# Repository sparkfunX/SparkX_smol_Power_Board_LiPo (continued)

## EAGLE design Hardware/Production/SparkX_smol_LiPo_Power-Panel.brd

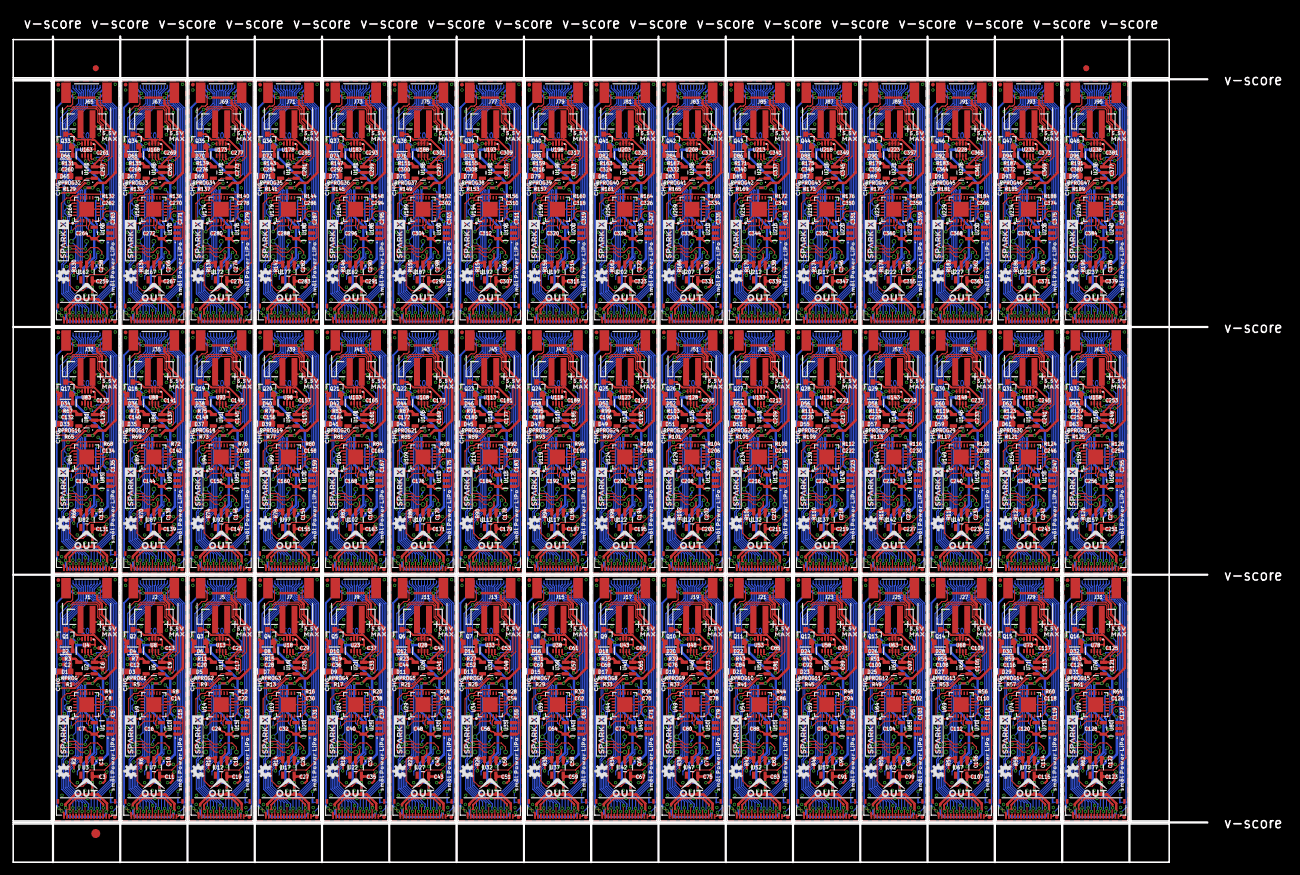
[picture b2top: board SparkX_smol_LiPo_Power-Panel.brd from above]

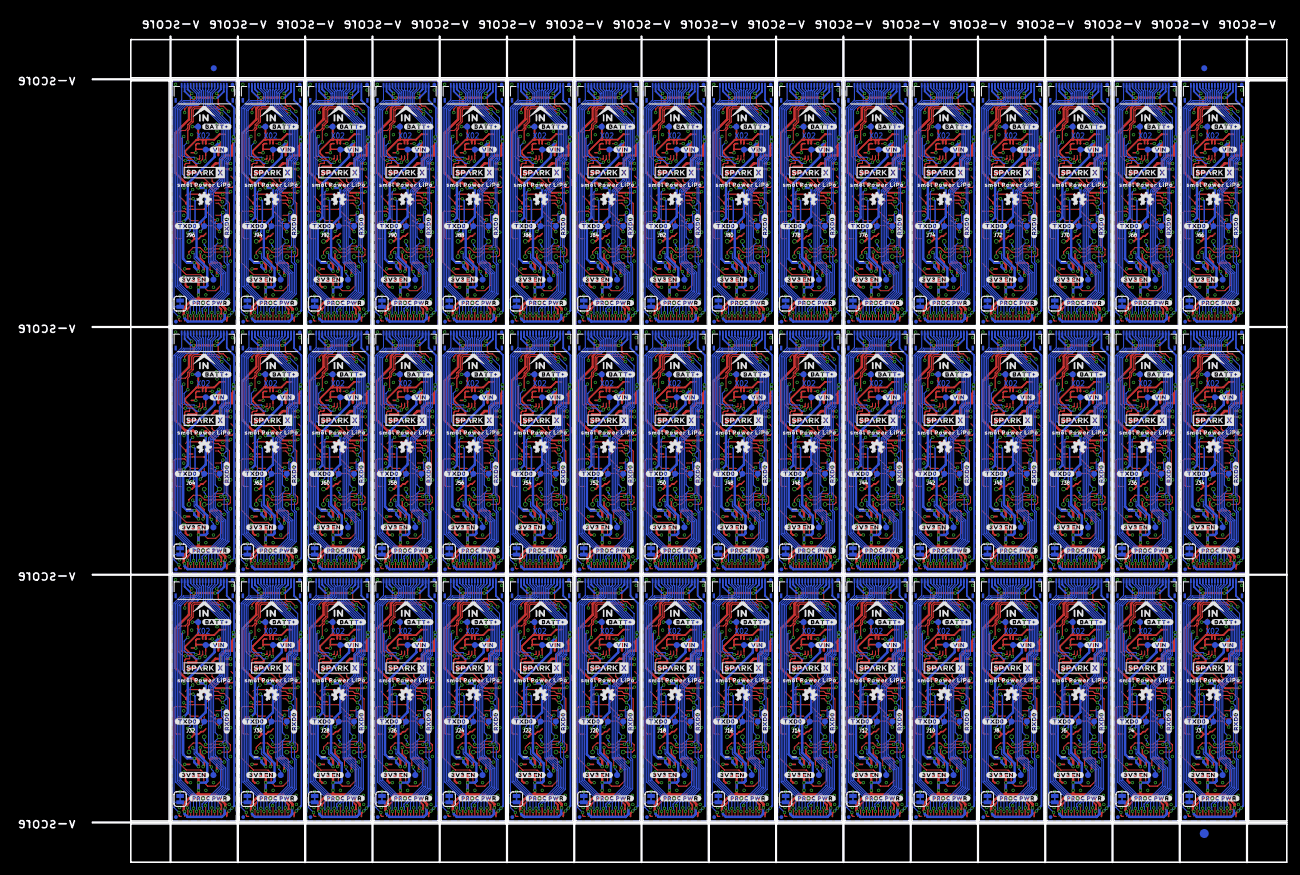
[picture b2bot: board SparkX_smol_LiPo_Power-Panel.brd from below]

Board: 2 copper layers, 198.4 x 137.2 mm, 2598 parts (1011 on the bottom side), 1200 nets.

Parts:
3V3_EN, 3V3_EN1, 3V3_EN2, 3V3_EN3, 3V3_EN4, 3V3_EN5, 3V3_EN6, 3V3_EN7, 3V3_EN8, 3V3_EN9, 3V3_EN10, 3V3_EN11, 3V3_EN12, 3V3_EN13, 3V3_EN14, 3V3_EN15, 3V3_EN16, 3V3_EN17, 3V3_EN18, 3V3_EN19, 3V3_EN20, 3V3_EN21, 3V3_EN22, 3V3_EN23, 3V3_EN24, 3V3_EN25, 3V3_EN26, 3V3_EN27, 3V3_EN28, 3V3_EN29, 3V3_EN30, 3V3_EN31, 3V3_EN32, 3V3_EN33, 3V3_EN34, 3V3_EN35, 3V3_EN36, 3V3_EN37, 3V3_EN38, 3V3_EN39, 3V3_EN40, 3V3_EN41, 3V3_EN42, 3V3_EN43, 3V3_EN44, 3V3_EN45, 3V3_EN46, 3V3_EN47: TEST-POINT3X4; PAD.03X.04
BATT+, BATT+1, BATT+2, BATT+3, BATT+4, BATT+5, BATT+6, BATT+7, BATT+8, BATT+9, BATT+10, BATT+11, BATT+12, BATT+13, BATT+14, BATT+15, BATT+16, BATT+17, BATT+18, BATT+19, BATT+20, BATT+21, BATT+22, BATT+23, BATT+24, BATT+25, BATT+26, BATT+27, BATT+28, BATT+29, BATT+30, BATT+31, BATT+32, BATT+33, BATT+34, BATT+35, BATT+36, BATT+37, BATT+38, BATT+39, BATT+40, BATT+41, BATT+42, BATT+43, BATT+44, BATT+45, BATT+46, BATT+47: TEST-POINT3X4; PAD.03X.04
C1, C2, C3, C5, C7, C10, C11, C12, C15, C16, C18, C19, C20, C23, C24, C26, C27, C28, C31, C32, C34, C35, C36, C39, C40, C42, C43, C44, C47, C48, C50, C51, C52, C55, C56, C58, C59, C60, C63, C64, C66, C67, C68, C71, C72, C74, C75, C76, C79, C80, C82, C83, C84, C87, C88, C90, C91, C92, C95, C96, C98, C99, C100, C103, C104, C106, C107, C108, C111, C112, C114, C115, C116, C119, C120, C122, C123, C124, C127, C128, C130, C131, C132, C135, C136, C138, C139, C140, C143, C144, C146, C147, C148, C151, C152, C154, C155, C156, C159, C160, C162, C163, C164, C167, C168, C170, C171, C172, C175, C176, C178, C179, C180, C183, C184, C186, C187, C188, C191, C192, C194, C195, C196, C199, C200, C202, C203, C204, C207, C208, C210, C211, C212, C215, C216, C218, C219, C220, C223, C224, C226, C227, C228, C231, C232, C234, C235, C236, C239, C240, C242, C243, C244, C247, C248, C250, C251, C252, C255, C256, C258, C259, C260, C263, C264, C266, C267, C268, C271, C272, C274, C275, C276, C279, C280, C282, C283, C284, C287, C288, C290, C291, C292, C295, C296, C298, C299, C300, C303, C304, C306, C307, C308, C311, C312, C314, C315, C316, C319, C320, C322, C323, C324, C327, C328, C330, C331, C332, C335, C336, C338, C339, C340, C343, C344, C346, C347, C348, C351, C352, C354, C355, C356, C359, C360, C362, C363, C364, C367, C368, C370, C371, C372, C375, C376, C378, C379, C380, C383, C384: 2.2uF; 0402-TIGHT
C4, C8, C13, C14, C21, C22, C29, C30, C37, C38, C45, C46, C53, C54, C61, C62, C69, C70, C77, C78, C85, C86, C93, C94, C101, C102, C109, C110, C117, C118, C125, C126, C133, C134, C141, C142, C149, C150, C157, C158, C165, C166, C173, C174, C181, C182, C189, C190, C197, C198, C205, C206, C213, C214, C221, C222, C229, C230, C237, C238, C245, C246, C253, C254, C261, C262, C269, C270, C277, C278, C285, C286, C293, C294, C301, C302, C309, C310, C317, C318, C325, C326, C333, C334, C341, C342, C349, C350, C357, C358, C365, C366, C373, C374, C381, C382: 0.1uF; 0402-TIGHT
C6, C9, C17, C25, C33, C41, C49, C57, C65, C73, C81, C89, C97, C105, C113, C121, C129, C137, C145, C153, C161, C169, C177, C185, C193, C201, C209, C217, C225, C233, C241, C249, C257, C265, C273, C281, C289, C297, C305, C313, C321, C329, C337, C345, C353, C361, C369, C377: 4.7uF; 0402-TIGHT
D1, D3, D5, D7, D9, D11, D13, D15, D17, D19, D21, D23, D25, D27, D29, D31, D33, D35, D37, D39, D41, D43, D45, D47, D49, D51, D53, D55, D57, D59, D61, D63, D65, D67, D69, D71, D73, D75, D77, D79, D81, D83, D85, D87, D89, D91, D93, D95: Yellow; LED-0603
D2, D4, D6, D8, D10, D12, D14, D16, D18, D20, D22, D24, D26, D28, D30, D32, D34, D36, D38, D40, D42, D44, D46, D48, D50, D52, D54, D56, D58, D60, D62, D64, D66, D68, D70, D72, D74, D76, D78, D80, D82, D84, D86, D88, D90, D92, D94, D96: 1A/23V/620mV; SOD-323
E$1, E$2, E$3, E$4: FIDUCIAL-1X2
E$5, E$6: FIDUCIAL-1.5X3
FD1, FD2, FD3, FD4, FD5, FD6, FD7, FD8, FD9, FD10, FD11, FD12, FD13, FD14, FD15, FD16, FD17, FD18, FD19, FD20, FD21, FD22, FD23, FD24, FD25, FD26, FD27, FD28, FD29, FD30, FD31, FD32, FD33, FD34, FD35, FD36, FD37, FD38, FD39, FD40, FD41, FD42, FD43, FD44, FD45, FD46, FD47, FD48, FD49, FD50, FD51, FD52, FD53, FD54, FD55, FD56, FD57, FD58, FD59, FD60, FD61, FD62, FD63, FD64, FD65, FD66, FD67, FD68, FD69, FD70, FD71, FD72, FD73, FD74, FD75, FD76, FD77, FD78, FD79, FD80, FD81, FD82, FD83, FD84, FD85, FD86, FD87, FD88, FD89, FD90, FD91, FD92, FD93, FD94, FD95, FD96, FD97, FD98, FD99, FD100, FD101, FD102, FD103, FD104, FD105, FD106, FD107, FD108, FD109, FD110, FD111, FD112, FD113, FD114, FD115, FD116, FD117, FD118, FD119, FD120, FD121, FD122, FD123, FD124, FD125, FD126, FD127, FD128, FD129, FD130, FD131, FD132, FD133, FD134, FD135, FD136, FD137, FD138, FD139, FD140, FD141, FD142, FD143, FD144, FD145, FD146, FD147, FD148, FD149, FD150, FD151, FD152, FD153, FD154, FD155, FD156, FD157, FD158, FD159, FD160, FD161, FD162, FD163, FD164, FD165, FD166, FD167, FD168, FD169, FD170, FD171, FD172, FD173, FD174, FD175, FD176, FD177, FD178, FD179, FD180, FD181, FD182, FD183, FD184, FD185, FD186, FD187, FD188, FD189, FD190, FD191, FD192: FIDUCIALUFIDUCIAL; FIDUCIAL-MICRO
IN, IN1, IN2, IN3, IN4, IN5, IN6, IN7, IN8, IN9, IN10, IN11, IN12, IN13, IN14, IN15, IN16, IN17, IN18, IN19, IN20, IN21, IN22, IN23, IN24, IN25, IN26, IN27, IN28, IN29, IN30, IN31, IN32, IN33, IN34, IN35, IN36, IN37, IN38, IN39, IN40, IN41, IN42, IN43, IN44, IN45, IN46, IN47: FPC_16_0.5MM
J1, J2, J5, J7, J9, J11, J13, J15, J17, J19, J21, J23, J25, J27, J29, J31, J33, J35, J37, J39, J41, J43, J45, J47, J49, J51, J53, J55, J57, J59, J61, J63, J65, J67, J69, J71, J73, J75, J77, J79, J81, J83, J85, J87, J89, J91, J93, J95: JST-2-SMD
J3, J4, J6, J8, J10, J12, J14, J16, J18, J20, J22, J24, J26, J28, J30, J32, J34, J36, J38, J40, J42, J44, J46, J48, J50, J52, J54, J56, J58, J60, J62, J64, J66, J68, J70, J72, J74, J76, J78, J80, J82, J84, J86, J88, J90, J92, J94, J96: AVR_SPI_PROG_3X2TESTPOINTS; 2X3_TEST_POINTS
LOGO1, LOGO2, LOGO3, LOGO4, LOGO5, LOGO6, LOGO7, LOGO8, LOGO9, LOGO10, LOGO11, LOGO12, LOGO13, LOGO14, LOGO15, LOGO16, LOGO17, LOGO18, LOGO19, LOGO20, LOGO21, LOGO22, LOGO23, LOGO24, LOGO25, LOGO26, LOGO27, LOGO28, LOGO29, LOGO30, LOGO31, LOGO32, LOGO33, LOGO34, LOGO35, LOGO36, LOGO37, LOGO38, LOGO39, LOGO40, LOGO41, LOGO42, LOGO43, LOGO44, LOGO45, LOGO46, LOGO47, LOGO48, LOGO49, LOGO50, LOGO51, LOGO52, LOGO53, LOGO54, LOGO55, LOGO56, LOGO57, LOGO58, LOGO59, LOGO60, LOGO61, LOGO62, LOGO63, LOGO64, LOGO65, LOGO66, LOGO67, LOGO68, LOGO69, LOGO70, LOGO71, LOGO72, LOGO73, LOGO74, LOGO75, LOGO76, LOGO77, LOGO78, LOGO79, LOGO80, LOGO81, LOGO82, LOGO83, LOGO84, LOGO85, LOGO86, LOGO87, LOGO88, LOGO89, LOGO90, LOGO91, LOGO92, LOGO93, LOGO94, LOGO95, LOGO96: OSHW-LOGOMINI; OSHW-LOGO-MINI
OUT, OUT1, OUT2, OUT3, OUT4, OUT5, OUT6, OUT7, OUT8, OUT9, OUT10, OUT11, OUT12, OUT13, OUT14, OUT15, OUT16, OUT17, OUT18, OUT19, OUT20, OUT21, OUT22, OUT23, OUT24, OUT25, OUT26, OUT27, OUT28, OUT29, OUT30, OUT31, OUT32, OUT33, OUT34, OUT35, OUT36, OUT37, OUT38, OUT39, OUT40, OUT41, OUT42, OUT43, OUT44, OUT45, OUT46, OUT47: FPC_16_0.5MM
PROC_PWR_EN, PROC_PWR_EN1, PROC_PWR_EN2, PROC_PWR_EN3, PROC_PWR_EN4, PROC_PWR_EN5, PROC_PWR_EN6, PROC_PWR_EN7, PROC_PWR_EN8, PROC_PWR_EN9, PROC_PWR_EN10, PROC_PWR_EN11, PROC_PWR_EN12, PROC_PWR_EN13, PROC_PWR_EN14, PROC_PWR_EN15, PROC_PWR_EN16, PROC_PWR_EN17, PROC_PWR_EN18, PROC_PWR_EN19, PROC_PWR_EN20, PROC_PWR_EN21, PROC_PWR_EN22, PROC_PWR_EN23, PROC_PWR_EN24, PROC_PWR_EN25, PROC_PWR_EN26, PROC_PWR_EN27, PROC_PWR_EN28, PROC_PWR_EN29, PROC_PWR_EN30, PROC_PWR_EN31, PROC_PWR_EN32, PROC_PWR_EN33, PROC_PWR_EN34, PROC_PWR_EN35, PROC_PWR_EN36, PROC_PWR_EN37, PROC_PWR_EN38, PROC_PWR_EN39, PROC_PWR_EN40, PROC_PWR_EN41, PROC_PWR_EN42, PROC_PWR_EN43, PROC_PWR_EN44, PROC_PWR_EN45, PROC_PWR_EN46, PROC_PWR_EN47: JUMPER-SMT_2_NC_TRACE_SILK; SMT-JUMPER_2_NC_TRACE_SILK
Q1, Q2, Q3, Q4, Q5, Q6, Q7, Q8, Q9, Q10, Q11, Q12, Q13, Q14, Q15, Q16, Q17, Q18, Q19, Q20, Q21, Q22, Q23, Q24, Q25, Q26, Q27, Q28, Q29, Q30, Q31, Q32, Q33, Q34, Q35, Q36, Q37, Q38, Q39, Q40, Q41, Q42, Q43, Q44, Q45, Q46, Q47, Q48: 3.1A/30V/105mΩ; SOT23-3
R1, R5, R9, R13, R17, R21, R25, R29, R33, R37, R41, R45, R49, R53, R57, R61, R65, R69, R73, R77, R81, R85, R89, R93, R97, R101, R105, R109, R113, R117, R121, R125, R129, R133, R137, R141, R145, R149, R153, R157, R161, R165, R169, R173, R177, R181, R185, R189: 1k; 0402-TIGHT
R2, R3, R6, R7, R10, R11, R14, R15, R18, R19, R22, R23, R26, R27, R30, R31, R34, R35, R38, R39, R42, R43, R46, R47, R50, R51, R54, R55, R58, R59, R62, R63, R66, R67, R70, R71, R74, R75, R78, R79, R82, R83, R86, R87, R90, R91, R94, R95, R98, R99, R102, R103, R106, R107, R110, R111, R114, R115, R118, R119, R122, R123, R126, R127, R130, R131, R134, R135, R138, R139, R142, R143, R146, R147, R150, R151, R154, R155, R158, R159, R162, R163, R166, R167, R170, R171, R174, R175, R178, R179, R182, R183, R186, R187, R190, R191: 100k; 0402-TIGHT
R4, R8, R12, R16, R20, R24, R28, R32, R36, R40, R44, R48, R52, R56, R60, R64, R68, R72, R76, R80, R84, R88, R92, R96, R100, R104, R108, R112, R116, R120, R124, R128, R132, R136, R140, R144, R148, R152, R156, R160, R164, R168, R172, R176, R180, R184, R188, R192: 4.7k; 0402-TIGHT
RPROG, RPROG1, RPROG2, RPROG3, RPROG4, RPROG5, RPROG6, RPROG7, RPROG8, RPROG9, RPROG10, RPROG11, RPROG12, RPROG13, RPROG14, RPROG15, RPROG16, RPROG17, RPROG18, RPROG19, RPROG20, RPROG21, RPROG22, RPROG23, RPROG24, RPROG25, RPROG26, RPROG27, RPROG28, RPROG29, RPROG30, RPROG31, RPROG32, RPROG33, RPROG34, RPROG35, RPROG36, RPROG37, RPROG38, RPROG39, RPROG40, RPROG41, RPROG42, RPROG43, RPROG44, RPROG45, RPROG46, RPROG47: 10k; 0402-TIGHT
RXD0, RXD1, RXD2, RXD3, RXD4, RXD5, RXD6, RXD7, RXD8, RXD9, RXD10, RXD11, RXD12, RXD13, RXD14, RXD15, RXD16, RXD17, RXD18, RXD19, RXD20, RXD21, RXD22, RXD23, RXD24, RXD25, RXD26, RXD27, RXD28, RXD29, RXD30, RXD31, RXD32, RXD33, RXD34, RXD35, RXD36, RXD37, RXD38, RXD39, RXD40, RXD41, RXD42, RXD43, RXD44, RXD45, RXD46, RXD47: TEST-POINT3X4; PAD.03X.04
TXD0, TXD1, TXD2, TXD3, TXD4, TXD5, TXD6, TXD7, TXD8, TXD9, TXD10, TXD11, TXD12, TXD13, TXD14, TXD15, TXD16, TXD17, TXD18, TXD19, TXD20, TXD21, TXD22, TXD23, TXD24, TXD25, TXD26, TXD27, TXD28, TXD29, TXD30, TXD31, TXD32, TXD33, TXD34, TXD35, TXD36, TXD37, TXD38, TXD39, TXD40, TXD41, TXD42, TXD43, TXD44, TXD45, TXD46, TXD47: TEST-POINT3X4; PAD.03X.04
U1, U10, U15, U20, U25, U30, U35, U40, U45, U50, U55, U60, U65, U70, U75, U80, U85, U90, U95, U100, U105, U110, U115, U120, U125, U130, U135, U140, U145, U150, U155, U160, U165, U170, U175, U180, U185, U190, U195, U200, U205, U210, U215, U220, U225, U230, U235, U240: STLQ015-3.3V; SOT23-5
U2, U6, U11, U16, U21, U26, U31, U36, U41, U46, U51, U56, U61, U66, U71, U76, U81, U86, U91, U96, U101, U106, U111, U116, U121, U126, U131, U136, U141, U146, U151, U156, U161, U166, U171, U176, U181, U186, U191, U196, U201, U206, U211, U216, U221, U226, U231, U236: MCP73831; SOT23-5
U3, U7, U12, U17, U22, U27, U32, U37, U42, U47, U52, U57, U62, U67, U72, U77, U82, U87, U92, U97, U102, U107, U112, U117, U122, U127, U132, U137, U142, U147, U152, U157, U162, U167, U172, U177, U182, U187, U192, U197, U202, U207, U212, U217, U222, U227, U232, U237: 3.3V; SOT23-5
U4, U8, U13, U18, U23, U28, U33, U38, U43, U48, U53, U58, U63, U68, U73, U78, U83, U88, U93, U98, U103, U108, U113, U118, U123, U128, U133, U138, U143, U148, U153, U158, U163, U168, U173, U178, U183, U188, U193, U198, U203, U208, U213, U218, U223, U228, U233, U238: MAX17048; DFN-8
U5, U9, U14, U19, U24, U29, U34, U39, U44, U49, U54, U59, U64, U69, U74, U79, U84, U89, U94, U99, U104, U109, U114, U119, U124, U129, U134, U139, U144, U149, U154, U159, U164, U169, U174, U179, U184, U189, U194, U199, U204, U209, U214, U219, U224, U229, U234, U239: ATTINY841-ARDUINO_QFN20M1; QFN20_20M1
U$1, U$12, U$13, U$20, U$35, U$36, U$52, U$53, U$69, U$70, U$86, U$87, U$103, U$104, U$120, U$121, U$137, U$138, U$154, U$155, U$171, U$172, U$188, U$189, U$205, U$206, U$222, U$223, U$239, U$240, U$256, U$257, U$273, U$274, U$290, U$291, U$307, U$308, U$324, U$325, U$341, U$342, U$358, U$359, U$375, U$376, U$392, U$393, U$409, U$410, U$426, U$427, U$443, U$444, U$460, U$461, U$477, U$478, U$494, U$495, U$511, U$512, U$528, U$529, U$545, U$546, U$562, U$563, U$579, U$580, U$596, U$597, U$613, U$614, U$630, U$631, U$647, U$648, U$664, U$665, U$681, U$682, U$698, U$699, U$715, U$716, U$732, U$733, U$749, U$750, U$766, U$767, U$783, U$784, U$800, U$801: SPARKX-LOGO3; SPARKX-SMALL
U$2, U$18, U$31, U$32, U$48, U$49, U$65, U$66, U$82, U$83, U$99, U$100, U$116, U$117, U$133, U$134, U$150, U$151, U$167, U$168, U$184, U$185, U$201, U$202, U$218, U$219, U$235, U$236, U$252, U$253, U$269, U$270, U$286, U$287, U$303, U$304, U$320, U$321, U$337, U$338, U$354, U$355, U$371, U$372, U$388, U$389, U$405, U$406, U$422, U$423, U$439, U$440, U$456, U$457, U$473, U$474, U$490, U$491, U$507, U$508, U$524, U$525, U$541, U$542, U$558, U$559, U$575, U$576, U$592, U$593, U$609, U$610, U$626, U$627, U$643, U$644, U$660, U$661, U$677, U$678, U$694, U$695, U$711, U$712, U$728, U$729, U$745, U$746, U$762, U$763, U$779, U$780, U$796, U$797, U$813, U$814: SM�L_POWER_LIPO0
U$3, U$9, U$33, U$34, U$50, U$51, U$67, U$68, U$84, U$85, U$101, U$102, U$118, U$119, U$135, U$136, U$152, U$153, U$169, U$170, U$186, U$187, U$203, U$204, U$220, U$221, U$237, U$238, U$254, U$255, U$271, U$272, U$288, U$289, U$305, U$306, U$322, U$323, U$339, U$340, U$356, U$357, U$373, U$374, U$390, U$391, U$407, U$408, U$424, U$425, U$441, U$442, U$458, U$459, U$475, U$476, U$492, U$493, U$509, U$510, U$526, U$527, U$543, U$544, U$560, U$561, U$577, U$578, U$594, U$595, U$611, U$612, U$628, U$629, U$645, U$646, U$662, U$663, U$679, U$680, U$696, U$697, U$713, U$714, U$730, U$731, U$747, U$748, U$764, U$765, U$781, U$782, U$798, U$799, U$815, U$816: SMOL_LOGOSMALL; SMOL_SMALL
U$4, U$19, U$37, U$54, U$71, U$88, U$105, U$122, U$139, U$156, U$173, U$190, U$207, U$224, U$241, U$258, U$275, U$292, U$309, U$326, U$343, U$360, U$377, U$394, U$411, U$428, U$445, U$462, U$479, U$496, U$513, U$530, U$547, U$564, U$581, U$598, U$615, U$632, U$649, U$666, U$683, U$700, U$717, U$734, U$751, U$768, U$785, U$802: #BATT##0
U$5, U$21, U$38, U$55, U$72, U$89, U$106, U$123, U$140, U$157, U$174, U$191, U$208, U$225, U$242, U$259, U$276, U$293, U$310, U$327, U$344, U$361, U$378, U$395, U$412, U$429, U$446, U$463, U$480, U$497, U$514, U$531, U$548, U$565, U$582, U$599, U$616, U$633, U$650, U$667, U$684, U$701, U$718, U$735, U$752, U$769, U$786, U$803: #VIN#0
U$6, U$22, U$39, U$56, U$73, U$90, U$107, U$124, U$141, U$158, U$175, U$192, U$209, U$226, U$243, U$260, U$277, U$294, U$311, U$328, U$345, U$362, U$379, U$396, U$413, U$430, U$447, U$464, U$481, U$498, U$515, U$532, U$549, U$566, U$583, U$600, U$617, U$634, U$651, U$668, U$685, U$702, U$719, U$736, U$753, U$770, U$787, U$804: #3V3_EN#0
U$7, U$23, U$40, U$57, U$74, U$91, U$108, U$125, U$142, U$159, U$176, U$193, U$210, U$227, U$244, U$261, U$278, U$295, U$312, U$329, U$346, U$363, U$380, U$397, U$414, U$431, U$448, U$465, U$482, U$499, U$516, U$533, U$550, U$567, U$584, U$601, U$618, U$635, U$652, U$669, U$686, U$703, U$720, U$737, U$754, U$771, U$788, U$805: #PROC_PWR#0
U$8, U$29, U$46, U$63, U$80, U$97, U$114, U$131, U$148, U$165, U$182, U$199, U$216, U$233, U$250, U$267, U$284, U$301, U$318, U$335, U$352, U$369, U$386, U$403, U$420, U$437, U$454, U$471, U$488, U$505, U$522, U$539, U$556, U$573, U$590, U$607, U$624, U$641, U$658, U$675, U$692, U$709, U$726, U$743, U$760, U$777, U$794, U$811: IN0
U$10, U$24, U$41, U$58, U$75, U$92, U$109, U$126, U$143, U$160, U$177, U$194, U$211, U$228, U$245, U$262, U$279, U$296, U$313, U$330, U$347, U$364, U$381, U$398, U$415, U$432, U$449, U$466, U$483, U$500, U$517, U$534, U$551, U$568, U$585, U$602, U$619, U$636, U$653, U$670, U$687, U$704, U$721, U$738, U$755, U$772, U$789, U$806: CHG0
U$11, U$28, U$45, U$62, U$79, U$96, U$113, U$130, U$147, U$164, U$181, U$198, U$215, U$232, U$249, U$266, U$283, U$300, U$317, U$334, U$351, U$368, U$385, U$402, U$419, U$436, U$453, U$470, U$487, U$504, U$521, U$538, U$555, U$572, U$589, U$606, U$623, U$640, U$657, U$674, U$691, U$708, U$725, U$742, U$759, U$776, U$793, U$810: MAX0
U$14, U$25, U$42, U$59, U$76, U$93, U$110, U$127, U$144, U$161, U$178, U$195, U$212, U$229, U$246, U$263, U$280, U$297, U$314, U$331, U$348, U$365, U$382, U$399, U$416, U$433, U$450, U$467, U$484, U$501, U$518, U$535, U$552, U$569, U$586, U$603, U$620, U$637, U$654, U$671, U$688, U$705, U$722, U$739, U$756, U$773, U$790, U$807: #RXD0#0
U$15, U$26, U$43, U$60, U$77, U$94, U$111, U$128, U$145, U$162, U$179, U$196, U$213, U$230, U$247, U$264, U$281, U$298, U$315, U$332, U$349, U$366, U$383, U$400, U$417, U$434, U$451, U$468, U$485, U$502, U$519, U$536, U$553, U$570, U$587, U$604, U$621, U$638, U$655, U$672, U$689, U$706, U$723, U$740, U$757, U$774, U$791, U$808: #TXD0#0
U$16, U$27, U$44, U$61, U$78, U$95, U$112, U$129, U$146, U$163, U$180, U$197, U$214, U$231, U$248, U$265, U$282, U$299, U$316, U$333, U$350, U$367, U$384, U$401, U$418, U$435, U$452, U$469, U$486, U$503, U$520, U$537, U$554, U$571, U$588, U$605, U$622, U$639, U$656, U$673, U$690, U$707, U$724, U$741, U$758, U$775, U$792, U$809: 5#5V0
U$17, U$30, U$47, U$64, U$81, U$98, U$115, U$132, U$149, U$166, U$183, U$200, U$217, U$234, U$251, U$268, U$285, U$302, U$319, U$336, U$353, U$370, U$387, U$404, U$421, U$438, U$455, U$472, U$489, U$506, U$523, U$540, U$557, U$574, U$591, U$608, U$625, U$642, U$659, U$676, U$693, U$710, U$727, U$744, U$761, U$778, U$795, U$812: OUT0
VIN, VIN1, VIN2, VIN3, VIN4, VIN5, VIN6, VIN7, VIN8, VIN9, VIN10, VIN11, VIN12, VIN13, VIN14, VIN15, VIN16, VIN17, VIN18, VIN19, VIN20, VIN21, VIN22, VIN23, VIN24, VIN25, VIN26, VIN27, VIN28, VIN29, VIN30, VIN31, VIN32, VIN33, VIN34, VIN35, VIN36, VIN37, VIN38, VIN39, VIN40, VIN41, VIN42, VIN43, VIN44, VIN45, VIN46, VIN47: TEST-POINT3X4; PAD.03X.04

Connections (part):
3.3V: C3.1, IN.2, IN.15, OUT.2, OUT.15, U3.5
3.3V1: C11.1, IN1.2, IN1.15, OUT1.2, OUT1.15, U7.5
3.3V2: C19.1, IN2.2, IN2.15, OUT2.2, OUT2.15, U12.5
3.3V3: C27.1, IN3.2, IN3.15, OUT3.2, OUT3.15, U17.5
3.3V4: C35.1, IN4.2, IN4.15, OUT4.2, OUT4.15, U22.5
3.3V5: C43.1, IN5.2, IN5.15, OUT5.2, OUT5.15, U27.5
3.3V6: C51.1, IN6.2, IN6.15, OUT6.2, OUT6.15, U32.5
3.3V7: C59.1, IN7.2, IN7.15, OUT7.2, OUT7.15, U37.5
3.3V8: C67.1, IN8.2, IN8.15, OUT8.2, OUT8.15, U42.5
3.3V9: C75.1, IN9.2, IN9.15, OUT9.2, OUT9.15, U47.5
3.3V10: C83.1, IN10.2, IN10.15, OUT10.2, OUT10.15, U52.5
3.3V11: C91.1, IN11.2, IN11.15, OUT11.2, OUT11.15, U57.5
3.3V12: C99.1, IN12.2, IN12.15, OUT12.2, OUT12.15, U62.5
3.3V13: C107.1, IN13.2, IN13.15, OUT13.2, OUT13.15, U67.5
3.3V14: C115.1, IN14.2, IN14.15, OUT14.2, OUT14.15, U72.5
3.3V15: C123.1, IN15.2, IN15.15, OUT15.2, OUT15.15, U77.5
3.3V16: C131.1, IN16.2, IN16.15, OUT16.2, OUT16.15, U82.5
3.3V17: C139.1, IN17.2, IN17.15, OUT17.2, OUT17.15, U87.5
3.3V18: C147.1, IN18.2, IN18.15, OUT18.2, OUT18.15, U92.5
3.3V19: C155.1, IN19.2, IN19.15, OUT19.2, OUT19.15, U97.5
3.3V20: C163.1, IN20.2, IN20.15, OUT20.2, OUT20.15, U102.5
3.3V21: C171.1, IN21.2, IN21.15, OUT21.2, OUT21.15, U107.5
3.3V22: C179.1, IN22.2, IN22.15, OUT22.2, OUT22.15, U112.5
3.3V23: C187.1, IN23.2, IN23.15, OUT23.2, OUT23.15, U117.5
3.3V24: C195.1, IN24.2, IN24.15, OUT24.2, OUT24.15, U122.5
3.3V25: C203.1, IN25.2, IN25.15, OUT25.2, OUT25.15, U127.5
3.3V26: C211.1, IN26.2, IN26.15, OUT26.2, OUT26.15, U132.5
3.3V27: C219.1, IN27.2, IN27.15, OUT27.2, OUT27.15, U137.5
3.3V28: C227.1, IN28.2, IN28.15, OUT28.2, OUT28.15, U142.5
3.3V29: C235.1, IN29.2, IN29.15, OUT29.2, OUT29.15, U147.5
3.3V30: C243.1, IN30.2, IN30.15, OUT30.2, OUT30.15, U152.5
3.3V31: C251.1, IN31.2, IN31.15, OUT31.2, OUT31.15, U157.5
3.3V32: C259.1, IN32.2, IN32.15, OUT32.2, OUT32.15, U162.5
3.3V33: C267.1, IN33.2, IN33.15, OUT33.2, OUT33.15, U167.5
3.3V34: C275.1, IN34.2, IN34.15, OUT34.2, OUT34.15, U172.5
3.3V35: C283.1, IN35.2, IN35.15, OUT35.2, OUT35.15, U177.5
3.3V36: C291.1, IN36.2, IN36.15, OUT36.2, OUT36.15, U182.5
3.3V37: C299.1, IN37.2, IN37.15, OUT37.2, OUT37.15, U187.5
3.3V38: C307.1, IN38.2, IN38.15, OUT38.2, OUT38.15, U192.5
3.3V39: C315.1, IN39.2, IN39.15, OUT39.2, OUT39.15, U197.5
3.3V40: C323.1, IN40.2, IN40.15, OUT40.2, OUT40.15, U202.5
3.3V41: C331.1, IN41.2, IN41.15, OUT41.2, OUT41.15, U207.5
3.3V42: C339.1, IN42.2, IN42.15, OUT42.2, OUT42.15, U212.5
3.3V43: C347.1, IN43.2, IN43.15, OUT43.2, OUT43.15, U217.5
3.3V44: C355.1, IN44.2, IN44.15, OUT44.2, OUT44.15, U222.5
3.3V45: C363.1, IN45.2, IN45.15, OUT45.2, OUT45.15, U227.5
3.3V46: C371.1, IN46.2, IN46.15, OUT46.2, OUT46.15, U232.5
3.3V47: C379.1, IN47.2, IN47.15, OUT47.2, OUT47.15, U237.5
3V3_EN: 3V3_EN.1, R2.2, U3.3, U5.5
3V3_EN1: 3V3_EN1.1, R6.2, U7.3, U9.5
3V3_EN2: 3V3_EN2.1, R10.2, U12.3, U14.5
3V3_EN3: 3V3_EN3.1, R14.2, U17.3, U19.5
3V3_EN4: 3V3_EN4.1, R18.2, U22.3, U24.5
3V3_EN5: 3V3_EN5.1, R22.2, U27.3, U29.5
3V3_EN6: 3V3_EN6.1, R26.2, U32.3, U34.5
3V3_EN7: 3V3_EN7.1, R30.2, U37.3, U39.5
3V3_EN8: 3V3_EN8.1, R34.2, U42.3, U44.5
3V3_EN9: 3V3_EN9.1, R38.2, U47.3, U49.5
3V3_EN10: 3V3_EN10.1, R42.2, U52.3, U54.5
3V3_EN11: 3V3_EN11.1, R46.2, U57.3, U59.5
3V3_EN12: 3V3_EN12.1, R50.2, U62.3, U64.5
3V3_EN13: 3V3_EN13.1, R54.2, U67.3, U69.5
3V3_EN14: 3V3_EN14.1, R58.2, U72.3, U74.5
3V3_EN15: 3V3_EN15.1, R62.2, U77.3, U79.5
3V3_EN16: 3V3_EN16.1, R66.2, U82.3, U84.5
3V3_EN17: 3V3_EN17.1, R70.2, U87.3, U89.5
3V3_EN18: 3V3_EN18.1, R74.2, U92.3, U94.5
3V3_EN19: 3V3_EN19.1, R78.2, U97.3, U99.5
3V3_EN20: 3V3_EN20.1, R82.2, U102.3, U104.5
3V3_EN21: 3V3_EN21.1, R86.2, U107.3, U109.5
3V3_EN22: 3V3_EN22.1, R90.2, U112.3, U114.5
3V3_EN23: 3V3_EN23.1, R94.2, U117.3, U119.5
3V3_EN24: 3V3_EN24.1, R98.2, U122.3, U124.5
3V3_EN25: 3V3_EN25.1, R102.2, U127.3, U129.5
3V3_EN26: 3V3_EN26.1, R106.2, U132.3, U134.5
3V3_EN27: 3V3_EN27.1, R110.2, U137.3, U139.5
3V3_EN28: 3V3_EN28.1, R114.2, U142.3, U144.5
3V3_EN29: 3V3_EN29.1, R118.2, U147.3, U149.5
3V3_EN30: 3V3_EN30.1, R122.2, U152.3, U154.5
3V3_EN31: 3V3_EN31.1, R126.2, U157.3, U159.5
3V3_EN32: 3V3_EN32.1, R130.2, U162.3, U164.5
3V3_EN33: 3V3_EN33.1, R134.2, U167.3, U169.5
3V3_EN34: 3V3_EN34.1, R138.2, U172.3, U174.5
3V3_EN35: 3V3_EN35.1, R142.2, U177.3, U179.5
3V3_EN36: 3V3_EN36.1, R146.2, U182.3, U184.5
3V3_EN37: 3V3_EN37.1, R150.2, U187.3, U189.5
3V3_EN38: 3V3_EN38.1, R154.2, U192.3, U194.5
3V3_EN39: 3V3_EN39.1, R158.2, U197.3, U199.5
3V3_EN40: 3V3_EN40.1, R162.2, U202.3, U204.5
3V3_EN41: 3V3_EN41.1, R166.2, U207.3, U209.5
3V3_EN42: 3V3_EN42.1, R170.2, U212.3, U214.5
3V3_EN43: 3V3_EN43.1, R174.2, U217.3, U219.5
3V3_EN44: 3V3_EN44.1, R178.2, U222.3, U224.5
3V3_EN45: 3V3_EN45.1, R182.2, U227.3, U229.5
3V3_EN46: 3V3_EN46.1, R186.2, U232.3, U234.5
3V3_EN47: 3V3_EN47.1, R190.2, U237.3, U239.5
!RESET!: J3.5, R4.1, U5.13
!RESET!1: J4.5, R8.1, U9.13
!RESET!2: J6.5, R12.1, U14.13
!RESET!3: J8.5, R16.1, U19.13
!RESET!4: J10.5, R20.1, U24.13
!RESET!5: J12.5, R24.1, U29.13
!RESET!6: J14.5, R28.1, U34.13
!RESET!7: J16.5, R32.1, U39.13
!RESET!8: J18.5, R36.1, U44.13
!RESET!9: J20.5, R40.1, U49.13
!RESET!10: J22.5, R44.1, U54.13
!RESET!11: J24.5, R48.1, U59.13
!RESET!12: J26.5, R52.1, U64.13
!RESET!13: J28.5, R56.1, U69.13
!RESET!14: J30.5, R60.1, U74.13
!RESET!15: J32.5, R64.1, U79.13
!RESET!16: J34.5, R68.1, U84.13
!RESET!17: J36.5, R72.1, U89.13
!RESET!18: J38.5, R76.1, U94.13
!RESET!19: J40.5, R80.1, U99.13
!RESET!20: J42.5, R84.1, U104.13
!RESET!21: J44.5, R88.1, U109.13
!RESET!22: J46.5, R92.1, U114.13
!RESET!23: J48.5, R96.1, U119.13
!RESET!24: J50.5, R100.1, U124.13
!RESET!25: J52.5, R104.1, U129.13
!RESET!26: J54.5, R108.1, U134.13
!RESET!27: J56.5, R112.1, U139.13
!RESET!28: J58.5, R116.1, U144.13
!RESET!29: J60.5, R120.1, U149.13
!RESET!30: J62.5, R124.1, U154.13
!RESET!31: J64.5, R128.1, U159.13
!RESET!32: J66.5, R132.1, U164.13
!RESET!33: J68.5, R136.1, U169.13
!RESET!34: J70.5, R140.1, U174.13
!RESET!35: J72.5, R144.1, U179.13
!RESET!36: J74.5, R148.1, U184.13
!RESET!37: J76.5, R152.1, U189.13
!RESET!38: J78.5, R156.1, U194.13
!RESET!39: J80.5, R160.1, U199.13
!RESET!40: J82.5, R164.1, U204.13
!RESET!41: J84.5, R168.1, U209.13
!RESET!42: J86.5, R172.1, U214.13
!RESET!43: J88.5, R176.1, U219.13
!RESET!44: J90.5, R180.1, U224.13
!RESET!45: J92.5, R184.1, U229.13
!RESET!46: J94.5, R188.1, U234.13
!RESET!47: J96.5, R192.1, U239.13
AT_CIPO: J3.1, U5.20
AT_CIPO1: J4.1, U9.20
AT_CIPO2: J6.1, U14.20
AT_CIPO3: J8.1, U19.20
AT_CIPO4: J10.1, U24.20
AT_CIPO5: J12.1, U29.20
AT_CIPO6: J14.1, U34.20
AT_CIPO7: J16.1, U39.20
AT_CIPO8: J18.1, U44.20
AT_CIPO9: J20.1, U49.20
AT_CIPO10: J22.1, U54.20
AT_CIPO11: J24.1, U59.20
AT_CIPO12: J26.1, U64.20
AT_CIPO13: J28.1, U69.20
AT_CIPO14: J30.1, U74.20
AT_CIPO15: J32.1, U79.20
AT_CIPO16: J34.1, U84.20
AT_CIPO17: J36.1, U89.20
AT_CIPO18: J38.1, U94.20
AT_CIPO19: J40.1, U99.20
AT_CIPO20: J42.1, U104.20
AT_CIPO21: J44.1, U109.20
AT_CIPO22: J46.1, U114.20
AT_CIPO23: J48.1, U119.20
AT_CIPO24: J50.1, U124.20
AT_CIPO25: J52.1, U129.20
AT_CIPO26: J54.1, U134.20
AT_CIPO27: J56.1, U139.20
AT_CIPO28: J58.1, U144.20
AT_CIPO29: J60.1, U149.20
AT_CIPO30: J62.1, U154.20
AT_CIPO31: J64.1, U159.20
AT_CIPO32: J66.1, U164.20
AT_CIPO33: J68.1, U169.20
AT_CIPO34: J70.1, U174.20
AT_CIPO35: J72.1, U179.20
AT_CIPO36: J74.1, U184.20
AT_CIPO37: J76.1, U189.20
AT_CIPO38: J78.1, U194.20
AT_CIPO39: J80.1, U199.20
AT_CIPO40: J82.1, U204.20
AT_CIPO41: J84.1, U209.20
AT_CIPO42: J86.1, U214.20
AT_CIPO43: J88.1, U219.20
AT_CIPO44: J90.1, U224.20
AT_CIPO45: J92.1, U229.20
AT_CIPO46: J94.1, U234.20
AT_CIPO47: J96.1, U239.20
AT_VCC: C7.1, C8.1, J3.2, R4.2, U1.5, U5.9
AT_VCC1: C14.1, C16.1, J4.2, R8.2, U9.9, U10.5
AT_VCC2: C22.1, C24.1, J6.2, R12.2, U14.9, U15.5
AT_VCC3: C30.1, C32.1, J8.2, R16.2, U19.9, U20.5
AT_VCC4: C38.1, C40.1, J10.2, R20.2, U24.9, U25.5
AT_VCC5: C46.1, C48.1, J12.2, R24.2, U29.9, U30.5
AT_VCC6: C54.1, C56.1, J14.2, R28.2, U34.9, U35.5
AT_VCC7: C62.1, C64.1, J16.2, R32.2, U39.9, U40.5
AT_VCC8: C70.1, C72.1, J18.2, R36.2, U44.9, U45.5
AT_VCC9: C78.1, C80.1, J20.2, R40.2, U49.9, U50.5
AT_VCC10: C86.1, C88.1, J22.2, R44.2, U54.9, U55.5
AT_VCC11: C94.1, C96.1, J24.2, R48.2, U59.9, U60.5
AT_VCC12: C102.1, C104.1, J26.2, R52.2, U64.9, U65.5
AT_VCC13: C110.1, C112.1, J28.2, R56.2, U69.9, U70.5
AT_VCC14: C118.1, C120.1, J30.2, R60.2, U74.9, U75.5
AT_VCC15: C126.1, C128.1, J32.2, R64.2, U79.9, U80.5
AT_VCC16: C134.1, C136.1, J34.2, R68.2, U84.9, U85.5
AT_VCC17: C142.1, C144.1, J36.2, R72.2, U89.9, U90.5
AT_VCC18: C150.1, C152.1, J38.2, R76.2, U94.9, U95.5
AT_VCC19: C158.1, C160.1, J40.2, R80.2, U99.9, U100.5
AT_VCC20: C166.1, C168.1, J42.2, R84.2, U104.9, U105.5
AT_VCC21: C174.1, C176.1, J44.2, R88.2, U109.9, U110.5
AT_VCC22: C182.1, C184.1, J46.2, R92.2, U114.9, U115.5
AT_VCC23: C190.1, C192.1, J48.2, R96.2, U119.9, U120.5
AT_VCC24: C198.1, C200.1, J50.2, R100.2, U124.9, U125.5
AT_VCC25: C206.1, C208.1, J52.2, R104.2, U129.9, U130.5
AT_VCC26: C214.1, C216.1, J54.2, R108.2, U134.9, U135.5
AT_VCC27: C222.1, C224.1, J56.2, R112.2, U139.9, U140.5
AT_VCC28: C230.1, C232.1, J58.2, R116.2, U144.9, U145.5
AT_VCC29: C238.1, C240.1, J60.2, R120.2, U149.9, U150.5
AT_VCC30: C246.1, C248.1, J62.2, R124.2, U154.9, U155.5
AT_VCC31: C254.1, C256.1, J64.2, R128.2, U159.9, U160.5
AT_VCC32: C262.1, C264.1, J66.2, R132.2, U164.9, U165.5
AT_VCC33: C270.1, C272.1, J68.2, R136.2, U169.9, U170.5
AT_VCC34: C278.1, C280.1, J70.2, R140.2, U174.9, U175.5
AT_VCC35: C286.1, C288.1, J72.2, R144.2, U179.9, U180.5
AT_VCC36: C294.1, C296.1, J74.2, R148.2, U184.9, U185.5
AT_VCC37: C302.1, C304.1, J76.2, R152.2, U189.9, U190.5
AT_VCC38: C310.1, C312.1, J78.2, R156.2, U194.9, U195.5
AT_VCC39: C318.1, C320.1, J80.2, R160.2, U199.9, U200.5
AT_VCC40: C326.1, C328.1, J82.2, R164.2, U204.9, U205.5
AT_VCC41: C334.1, C336.1, J84.2, R168.2, U209.9, U210.5
AT_VCC42: C342.1, C344.1, J86.2, R172.2, U214.9, U215.5
AT_VCC43: C350.1, C352.1, J88.2, R176.2, U219.9, U220.5
AT_VCC44: C358.1, C360.1, J90.2, R180.2, U224.9, U225.5
AT_VCC45: C366.1, C368.1, J92.2, R184.2, U229.9, U230.5
AT_VCC46: C374.1, C376.1, J94.2, R188.2, U234.9, U235.5
AT_VCC47: C382.1, C384.1, J96.2, R192.2, U239.9, U240.5
CHG_LED: R1.1, U2.1
CHG_LED1: R5.1, U6.1
CHG_LED2: R9.1, U11.1
CHG_LED3: R13.1, U16.1
CHG_LED4: R17.1, U21.1
CHG_LED5: R21.1, U26.1
CHG_LED6: R25.1, U31.1
CHG_LED7: R29.1, U36.1
CHG_LED8: R33.1, U41.1
CHG_LED9: R37.1, U46.1
CHG_LED10: R41.1, U51.1
CHG_LED11: R45.1, U56.1
CHG_LED12: R49.1, U61.1
CHG_LED13: R53.1, U66.1
CHG_LED14: R57.1, U71.1
CHG_LED15: R61.1, U76.1
CHG_LED16: R65.1, U81.1
CHG_LED17: R69.1, U86.1
CHG_LED18: R73.1, U91.1
CHG_LED19: R77.1, U96.1
CHG_LED20: R81.1, U101.1
CHG_LED21: R85.1, U106.1
CHG_LED22: R89.1, U111.1
CHG_LED23: R93.1, U116.1
CHG_LED24: R97.1, U121.1
CHG_LED25: R101.1, U126.1
CHG_LED26: R105.1, U131.1
CHG_LED27: R109.1, U136.1
CHG_LED28: R113.1, U141.1
CHG_LED29: R117.1, U146.1
CHG_LED30: R121.1, U151.1
CHG_LED31: R125.1, U156.1
CHG_LED32: R129.1, U161.1
CHG_LED33: R133.1, U166.1
CHG_LED34: R137.1, U171.1
CHG_LED35: R141.1, U176.1
CHG_LED36: R145.1, U181.1
CHG_LED37: R149.1, U186.1
CHG_LED38: R153.1, U191.1
CHG_LED39: R157.1, U196.1
CHG_LED40: R161.1, U201.1
CHG_LED41: R165.1, U206.1
CHG_LED42: R169.1, U211.1
CHG_LED43: R173.1, U216.1
CHG_LED44: R177.1, U221.1
CHG_LED45: R181.1, U226.1
CHG_LED46: R185.1, U231.1
CHG_LED47: R189.1, U236.1
CIPO: IN.6, OUT.6
CIPO1: IN1.6, OUT1.6
CIPO2: IN2.6, OUT2.6
CIPO3: IN3.6, OUT3.6
CIPO4: IN4.6, OUT4.6
CIPO5: IN5.6, OUT5.6
CIPO6: IN6.6, OUT6.6
CIPO7: IN7.6, OUT7.6
CIPO8: IN8.6, OUT8.6
CIPO9: IN9.6, OUT9.6
CIPO10: IN10.6, OUT10.6
CIPO11: IN11.6, OUT11.6
CIPO12: IN12.6, OUT12.6
CIPO13: IN13.6, OUT13.6
CIPO14: IN14.6, OUT14.6
CIPO15: IN15.6, OUT15.6
CIPO16: IN16.6, OUT16.6
CIPO17: IN17.6, OUT17.6
CIPO18: IN18.6, OUT18.6
CIPO19: IN19.6, OUT19.6
CIPO20: IN20.6, OUT20.6
CIPO21: IN21.6, OUT21.6
CIPO22: IN22.6, OUT22.6
CIPO23: IN23.6, OUT23.6
CIPO24: IN24.6, OUT24.6
CIPO25: IN25.6, OUT25.6
CIPO26: IN26.6, OUT26.6
CIPO27: IN27.6, OUT27.6
CIPO28: IN28.6, OUT28.6
CIPO29: IN29.6, OUT29.6
CIPO30: IN30.6, OUT30.6
CIPO31: IN31.6, OUT31.6
CIPO32: IN32.6, OUT32.6
CIPO33: IN33.6, OUT33.6
CIPO34: IN34.6, OUT34.6
CIPO35: IN35.6, OUT35.6
CIPO36: IN36.6, OUT36.6
CIPO37: IN37.6, OUT37.6
CIPO38: IN38.6, OUT38.6
CIPO39: IN39.6, OUT39.6
CIPO40: IN40.6, OUT40.6
CIPO41: IN41.6, OUT41.6
CIPO42: IN42.6, OUT42.6
CIPO43: IN43.6, OUT43.6
CIPO44: IN44.6, OUT44.6
CIPO45: IN45.6, OUT45.6
CIPO46: IN46.6, OUT46.6
CIPO47: IN47.6, OUT47.6
COPI: IN.5, OUT.5
COPI1: IN1.5, OUT1.5
COPI2: IN2.5, OUT2.5
COPI3: IN3.5, OUT3.5
COPI4: IN4.5, OUT4.5
COPI5: IN5.5, OUT5.5
COPI6: IN6.5, OUT6.5
COPI7: IN7.5, OUT7.5
COPI8: IN8.5, OUT8.5
COPI9: IN9.5, OUT9.5
COPI10: IN10.5, OUT10.5
COPI11: IN11.5, OUT11.5
COPI12: IN12.5, OUT12.5
COPI13: IN13.5, OUT13.5
COPI14: IN14.5, OUT14.5
COPI15: IN15.5, OUT15.5
COPI16: IN16.5, OUT16.5
COPI17: IN17.5, OUT17.5
COPI18: IN18.5, OUT18.5
COPI19: IN19.5, OUT19.5
COPI20: IN20.5, OUT20.5
COPI21: IN21.5, OUT21.5
COPI22: IN22.5, OUT22.5
COPI23: IN23.5, OUT23.5
COPI24: IN24.5, OUT24.5
COPI25: IN25.5, OUT25.5
COPI26: IN26.5, OUT26.5
COPI27: IN27.5, OUT27.5
COPI28: IN28.5, OUT28.5
COPI29: IN29.5, OUT29.5
COPI30: IN30.5, OUT30.5
COPI31: IN31.5, OUT31.5
COPI32: IN32.5, OUT32.5
COPI33: IN33.5, OUT33.5
COPI34: IN34.5, OUT34.5
COPI35: IN35.5, OUT35.5
COPI36: IN36.5, OUT36.5
COPI37: IN37.5, OUT37.5
COPI38: IN38.5, OUT38.5
COPI39: IN39.5, OUT39.5
COPI40: IN40.5, OUT40.5
COPI41: IN41.5, OUT41.5
COPI42: IN42.5, OUT42.5
COPI43: IN43.5, OUT43.5
COPI44: IN44.5, OUT44.5
COPI45: IN45.5, OUT45.5
COPI46: IN46.5, OUT46.5
COPI47: IN47.5, OUT47.5
CS0: IN.7, OUT.7
CS1: IN.8, OUT.8
CS2: IN.9, OUT.9
CS3: IN1.7, OUT1.7
CS4: IN1.8, OUT1.8
CS5: IN1.9, OUT1.9
CS6: IN2.7, OUT2.7
CS7: IN2.8, OUT2.8
CS8: IN2.9, OUT2.9
CS9: IN3.7, OUT3.7
CS10: IN3.8, OUT3.8
CS11: IN3.9, OUT3.9
CS12: IN4.7, OUT4.7
CS13: IN4.8, OUT4.8
CS14: IN4.9, OUT4.9
CS15: IN5.7, OUT5.7
CS16: IN5.8, OUT5.8
CS17: IN5.9, OUT5.9
CS18: IN6.7, OUT6.7
CS19: IN6.8, OUT6.8
CS20: IN6.9, OUT6.9
CS21: IN7.7, OUT7.7
CS22: IN7.8, OUT7.8
CS23: IN7.9, OUT7.9
CS24: IN8.7, OUT8.7
CS25: IN8.8, OUT8.8
CS26: IN8.9, OUT8.9
CS27: IN9.7, OUT9.7
CS28: IN9.8, OUT9.8
CS29: IN9.9, OUT9.9
CS30: IN10.7, OUT10.7
CS31: IN10.8, OUT10.8
CS32: IN10.9, OUT10.9
CS33: IN11.7, OUT11.7
CS34: IN11.8, OUT11.8
CS35: IN11.9, OUT11.9
CS36: IN12.7, OUT12.7
CS37: IN12.8, OUT12.8
CS38: IN12.9, OUT12.9
CS39: IN13.7, OUT13.7
CS40: IN13.8, OUT13.8
CS41: IN13.9, OUT13.9
CS42: IN14.7, OUT14.7
CS43: IN14.8, OUT14.8
CS44: IN14.9, OUT14.9
CS45: IN15.7, OUT15.7
CS46: IN15.8, OUT15.8
CS47: IN15.9, OUT15.9
CS48: IN16.7, OUT16.7
CS49: IN16.8, OUT16.8
CS50: IN16.9, OUT16.9
CS51: IN17.7, OUT17.7
CS52: IN17.8, OUT17.8
CS53: IN17.9, OUT17.9
CS54: IN18.7, OUT18.7
CS55: IN18.8, OUT18.8
CS56: IN18.9, OUT18.9
CS57: IN19.7, OUT19.7
CS58: IN19.8, OUT19.8
CS59: IN19.9, OUT19.9
CS60: IN20.7, OUT20.7
CS61: IN20.8, OUT20.8
CS62: IN20.9, OUT20.9
CS63: IN21.7, OUT21.7
CS64: IN21.8, OUT21.8
CS65: IN21.9, OUT21.9
CS66: IN22.7, OUT22.7
CS67: IN22.8, OUT22.8
CS68: IN22.9, OUT22.9
CS69: IN23.7, OUT23.7
CS70: IN23.8, OUT23.8
CS71: IN23.9, OUT23.9
CS72: IN24.7, OUT24.7
CS73: IN24.8, OUT24.8
CS74: IN24.9, OUT24.9
CS75: IN25.7, OUT25.7
CS76: IN25.8, OUT25.8
CS77: IN25.9, OUT25.9
CS78: IN26.7, OUT26.7
CS79: IN26.8, OUT26.8
CS80: IN26.9, OUT26.9
CS81: IN27.7, OUT27.7
CS82: IN27.8, OUT27.8
CS83: IN27.9, OUT27.9
CS84: IN28.7, OUT28.7
CS85: IN28.8, OUT28.8
CS86: IN28.9, OUT28.9
CS87: IN29.7, OUT29.7
CS88: IN29.8, OUT29.8
CS89: IN29.9, OUT29.9
CS90: IN30.7, OUT30.7
CS91: IN30.8, OUT30.8
CS92: IN30.9, OUT30.9
CS93: IN31.7, OUT31.7
CS94: IN31.8, OUT31.8
CS95: IN31.9, OUT31.9
CS96: IN32.7, OUT32.7
CS97: IN32.8, OUT32.8
CS98: IN32.9, OUT32.9
CS99: IN33.7, OUT33.7
CS100: IN33.8, OUT33.8
CS101: IN33.9, OUT33.9
CS102: IN34.7, OUT34.7
CS103: IN34.8, OUT34.8
CS104: IN34.9, OUT34.9
CS105: IN35.7, OUT35.7
CS106: IN35.8, OUT35.8
CS107: IN35.9, OUT35.9
CS108: IN36.7, OUT36.7
CS109: IN36.8, OUT36.8
CS110: IN36.9, OUT36.9
CS111: IN37.7, OUT37.7
CS112: IN37.8, OUT37.8
CS113: IN37.9, OUT37.9
CS114: IN38.7, OUT38.7
CS115: IN38.8, OUT38.8
CS116: IN38.9, OUT38.9
CS117: IN39.7, OUT39.7
CS118: IN39.8, OUT39.8
CS119: IN39.9, OUT39.9
CS120: IN40.7, OUT40.7
CS121: IN40.8, OUT40.8
CS122: IN40.9, OUT40.9
CS123: IN41.7, OUT41.7
CS124: IN41.8, OUT41.8
CS125: IN41.9, OUT41.9
CS126: IN42.7, OUT42.7
CS127: IN42.8, OUT42.8
CS128: IN42.9, OUT42.9
CS129: IN43.7, OUT43.7
CS130: IN43.8, OUT43.8
CS131: IN43.9, OUT43.9
CS132: IN44.7, OUT44.7
CS133: IN44.8, OUT44.8
CS134: IN44.9, OUT44.9
CS135: IN45.7, OUT45.7
CS136: IN45.8, OUT45.8
CS137: IN45.9, OUT45.9
CS138: IN46.7, OUT46.7
CS139: IN46.8, OUT46.8
CS140: IN46.9, OUT46.9
CS141: IN47.7, OUT47.7
CS142: IN47.8, OUT47.8
CS143: IN47.9, OUT47.9
GND: C1.2, C2.2, C3.2, C4.2, C5.2, C6.2, C7.2, C8.2, IN.3, IN.14, J1.1, J3.6, OUT.3, OUT.14, PROC_PWR_EN.2, R2.1, R3.1, RPROG.1, U1.2, U2.2, U3.2, U4.1, U4.4, U4.6, U4.9, U5.8, U5.PAD
GND1: C9.2, C10.2, C11.2, C12.2, C13.2, C14.2, C15.2, C16.2, IN1.3, IN1.14, J2.1, J4.6, OUT1.3, OUT1.14, PROC_PWR_EN1.2, R6.1, R7.1, RPROG1.1, U6.2, U7.2, U8.1, U8.4, U8.6, U8.9, U9.8, U9.PAD, U10.2
GND2: C17.2, C18.2, C19.2, C20.2, C21.2, C22.2, C23.2, C24.2, IN2.3, IN2.14, J5.1, J6.6, OUT2.3, OUT2.14, PROC_PWR_EN2.2, R10.1, R11.1, RPROG2.1, U11.2, U12.2, U13.1, U13.4, U13.6, U13.9, U14.8, U14.PAD, U15.2
GND3: C25.2, C26.2, C27.2, C28.2, C29.2, C30.2, C31.2, C32.2, IN3.3, IN3.14, J7.1, J8.6, OUT3.3, OUT3.14, PROC_PWR_EN3.2, R14.1, R15.1, RPROG3.1, U16.2, U17.2, U18.1, U18.4, U18.6, U18.9, U19.8, U19.PAD, U20.2
GND4: C33.2, C34.2, C35.2, C36.2, C37.2, C38.2, C39.2, C40.2, IN4.3, IN4.14, J9.1, J10.6, OUT4.3, OUT4.14, PROC_PWR_EN4.2, R18.1, R19.1, RPROG4.1, U21.2, U22.2, U23.1, U23.4, U23.6, U23.9, U24.8, U24.PAD, U25.2
GND5: C41.2, C42.2, C43.2, C44.2, C45.2, C46.2, C47.2, C48.2, IN5.3, IN5.14, J11.1, J12.6, OUT5.3, OUT5.14, PROC_PWR_EN5.2, R22.1, R23.1, RPROG5.1, U26.2, U27.2, U28.1, U28.4, U28.6, U28.9, U29.8, U29.PAD, U30.2
GND6: C49.2, C50.2, C51.2, C52.2, C53.2, C54.2, C55.2, C56.2, IN6.3, IN6.14, J13.1, J14.6, OUT6.3, OUT6.14, PROC_PWR_EN6.2, R26.1, R27.1, RPROG6.1, U31.2, U32.2, U33.1, U33.4, U33.6, U33.9, U34.8, U34.PAD, U35.2
GND7: C57.2, C58.2, C59.2, C60.2, C61.2, C62.2, C63.2, C64.2, IN7.3, IN7.14, J15.1, J16.6, OUT7.3, OUT7.14, PROC_PWR_EN7.2, R30.1, R31.1, RPROG7.1, U36.2, U37.2, U38.1, U38.4, U38.6, U38.9, U39.8, U39.PAD, U40.2
GND8: C65.2, C66.2, C67.2, C68.2, C69.2, C70.2, C71.2, C72.2, IN8.3, IN8.14, J17.1, J18.6, OUT8.3, OUT8.14, PROC_PWR_EN8.2, R34.1, R35.1, RPROG8.1, U41.2, U42.2, U43.1, U43.4, U43.6, U43.9, U44.8, U44.PAD, U45.2
GND9: C73.2, C74.2, C75.2, C76.2, C77.2, C78.2, C79.2, C80.2, IN9.3, IN9.14, J19.1, J20.6, OUT9.3, OUT9.14, PROC_PWR_EN9.2, R38.1, R39.1, RPROG9.1, U46.2, U47.2, U48.1, U48.4, U48.6, U48.9, U49.8, U49.PAD, U50.2
GND10: C81.2, C82.2, C83.2, C84.2, C85.2, C86.2, C87.2, C88.2, IN10.3, IN10.14, J21.1, J22.6, OUT10.3, OUT10.14, PROC_PWR_EN10.2, R42.1, R43.1, RPROG10.1, U51.2, U52.2, U53.1, U53.4, U53.6, U53.9, U54.8, U54.PAD, U55.2
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
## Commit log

2021-05-17 Partially routed
2021-05-17 Freshly routed
2021-05-18 Ready for review
2021-05-25 Post-review updates
2021-05-26 Final tweaks
2021-05-27 Gapless production panel
2021-06-09 Update 16-way FPC Connector. Add missing PROD_IDs
2021-07-29 Add the firmware
2021-08-02 Correcting I2C restart-after-power-down problems
2021-08-18 X02 - changed to smol branding
2021-08-19 Update smol symbol
2021-08-20 Change EZ to smôl on schematic
2021-09-28 Change .hex filename to 8.3 format
2021-10-28 Add SKU and product image
